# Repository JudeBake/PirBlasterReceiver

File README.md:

# PirBlasterReceiver
Raspberry Pi IR Blaster Receiver

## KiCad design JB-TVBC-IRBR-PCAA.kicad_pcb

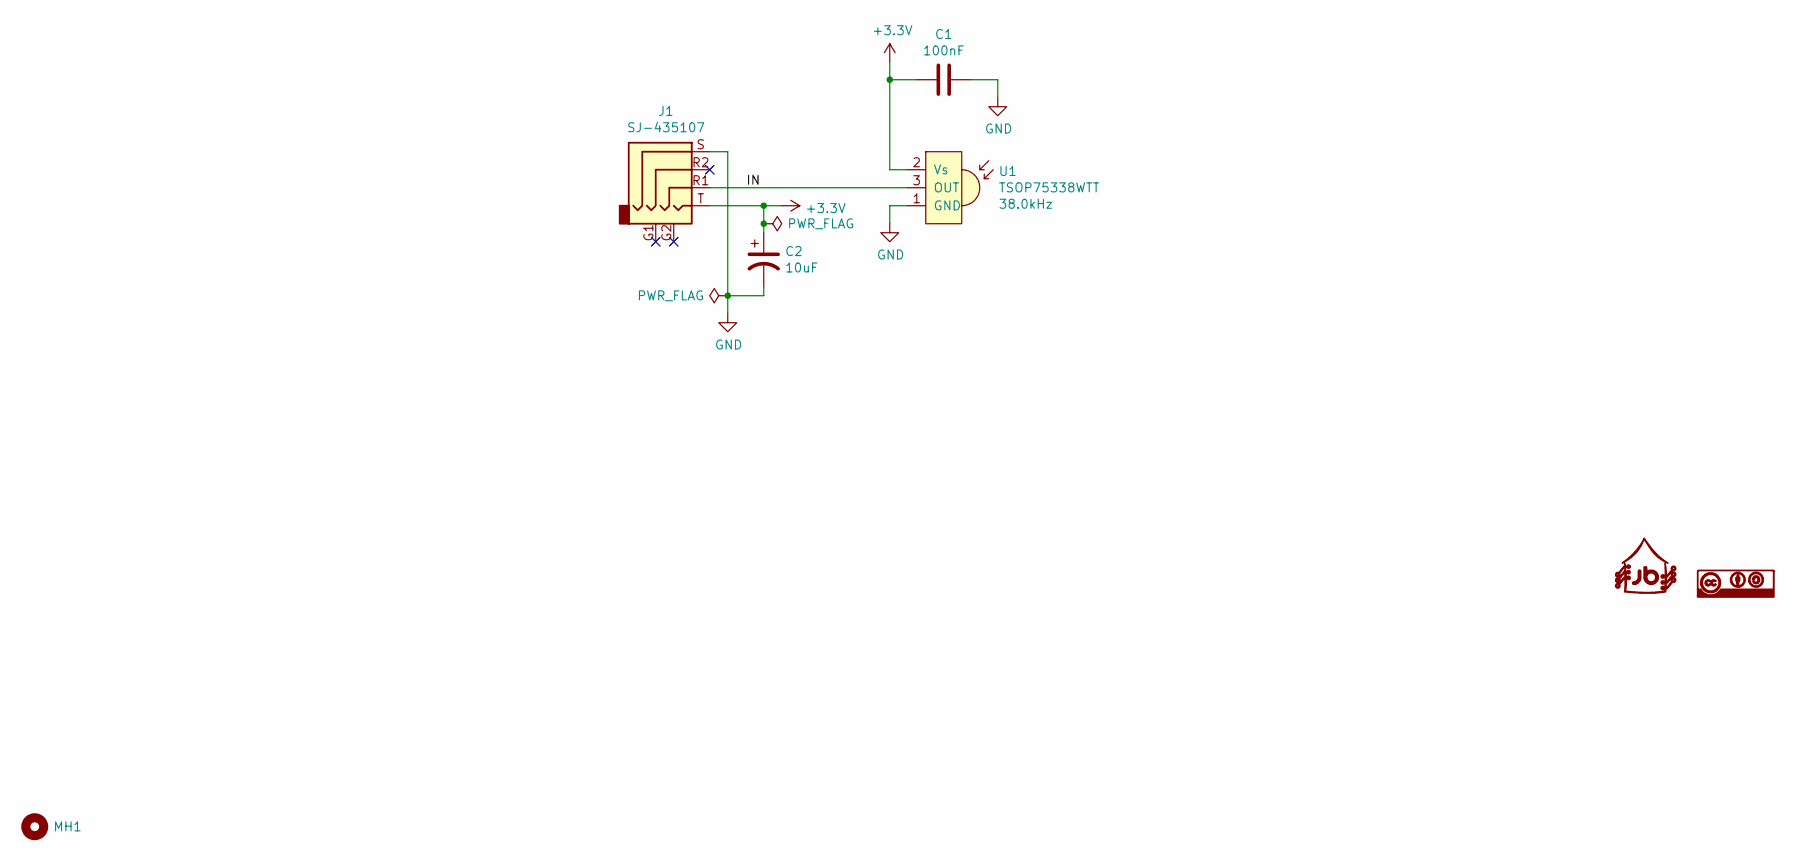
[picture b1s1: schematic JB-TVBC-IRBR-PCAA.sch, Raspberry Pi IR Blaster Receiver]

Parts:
C1: 100nF_CER_0603_50V; C_0603_1608Metric_Pad1.05x0.95mm_HandSolder; Manufacturer Part Number 06033D104MAT2A; Digi-Key Part Number 478-7905-2-ND
C2: 10UF_TANT_1206_16V; CP_EIA-3216-18_Kemet-A_Pad1.58x1.35mm_HandSolder; Manufacturer Part Number T491A106K016AT; Digi-Key Part Number 399-8269-2-ND
G1: JudeBake_Logo; JB_Logo_4MM
G2: CC-BY-SA_Logo; CC-BY-SA_4MM
J1: SJ-435107; Manufacturer Part Number SJ-435107; Digi-Key Part Number CP-435107-ND
MH1: TH-NPLTD-D5.2; TH-UPLTD-D5.2
U1: TSOP75338WTT; TSOP753xx_RA; Manufacturer Part Number TSOP75338WTT; Digi-Key Part Number TSOP75338WTTCT-ND

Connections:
+3V3: C1.2, C2.1, J1.T, U1.2 (Vs)
/IN: J1.R1, U1.3 (OUT)
GND: C1.1, C2.2, J1.S, U1.1 (GND), U1.4 (GND)

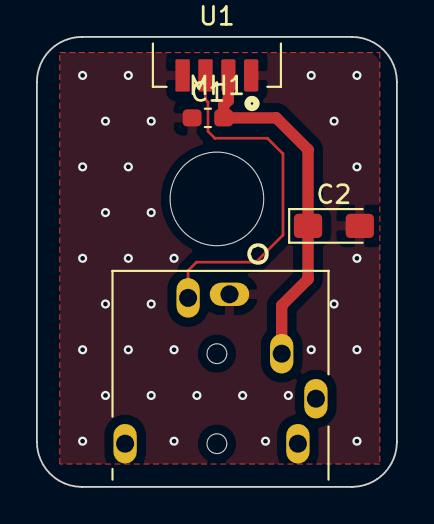
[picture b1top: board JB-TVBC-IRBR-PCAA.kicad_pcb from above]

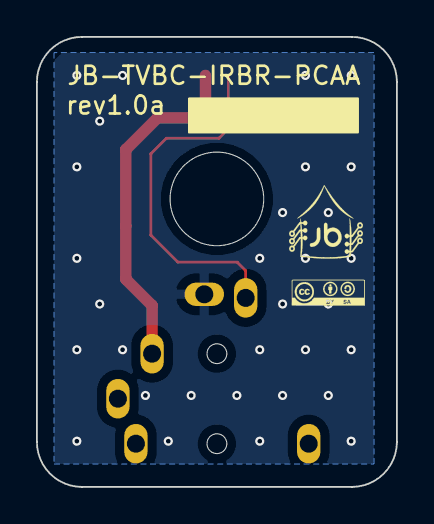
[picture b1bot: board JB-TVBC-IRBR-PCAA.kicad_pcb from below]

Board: 2 copper layers, 20.0 x 25.0 mm, 7 parts (2 on the bottom side), 3 nets.

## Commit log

2020-03-15 project creation + pcb routing done
2020-03-15 clearing case + ref designator positioning
2020-03-15 generating interactive bom
2020-03-15 last save
